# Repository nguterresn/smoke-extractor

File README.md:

# Welcome to the Smoke Extractor Repository!

Are you tired of inhaling smoke and fumes while soldering? Look no further! This portable smoke extractor is here to evolve your soldering experience.

This repository contains all the information you need to build your own smoke extractor using readily available components.

| [PCB](https://github.com/nguterresn/smoke-extractor/tree/master/pcb/1v1) | [STL](https://github.com/nguterresn/smoke-extractor/tree/master/stl) | [GERBER](https://github.com/nguterresn/smoke-extractor/blob/master/pcb/1v1/jlcpcb/production_files/GERBER-smoke_extractorV1_1.zip) | [BOM](https://github.com/nguterresn/smoke-extractor/blob/master/pcb/1v1/jlcpcb/production_files/BOM-smoke_extractorV1_1.csv) |
|-----|-----|--------|-----|

Below is a list of what you need. Let's start with the PCB:

* Take the [Bill of Materials](https://github.com/nguterresn/smoke-extractor/blob/master/pcb/1v1/jlcpcb/production_files/BOM-smoke_extractorV1_1.csv) and order from [LCSC](https://www.lcsc.com).
* Take the [compressed gerber files](https://github.com/nguterresn/smoke-extractor/blob/master/pcb/1v1/jlcpcb/production_files/GERBER-smoke_extractorV1_1.zip) and order the PCB from [JLCPCB](https://jlcpcb.com)

To 3D print the [enclosure](https://github.com/nguterresn/smoke-extractor/tree/master/stl/1v1), I would recommend to print it vertically with supports only where the PCB fits and at the top.

* You can find the files for the enclosure at [Thinginverse](https://www.thingiverse.com/thing:6496883) or on the [repository](https://github.com/nguterresn/smoke-extractor/tree/master/stl/1v1).
* You can find the sliced model and ready to print file for BambuLab printers here.

And finally, necessary items you can find in Amazon:

* Buy the Fume's filter. I took a [filter used on cat litter boxes](https://www.amazon.se/gp/product/B07WJ1Y1CH/ref=ppx_yo_dt_b_asin_title_o08_s00?ie=UTF8&psc=1) and trimmed it to 80x80mm.
* Buy a [80x80x25mm 12V fan](https://www.amazon.se/-/en/1-06W-80x80x25mm-56-1m³-2600U-EE80251S31000U999/dp/B07ZBNZQ2S/ref=sr_1_3?crid=MVLR8KCZBU2A&dib=eyJ2IjoiMSJ9.yyIoiUBXEqPdx7PXhLvxQ6DgrM7XN99XWWnRf-wjLIC2jV-B3UQ4XywT_NGIYMAKHvOpfRhJtW1-Edui-ORV4xDNA9OV7_BThwgb9X33OIwgTvXAGk9CamoQANMFjjYQfQlXwd1fQ9uBfTSz37shrT1HXBxxIDawscOyjEqbqhflptzGCS32OoU-07Krv_tXsq_2aFJ8kRP7iFG2Fm3--l_kvcWPGcEGKE2OmgzGbOBmr5wPGlOs1hTMt8ZC6lYbEhc1kAilJPhcBsXh4ESUahyO5wKTHMeF1VTbrVZGBB4.kkiZ6oj-aX831UgWn2JdLQOQZ6zxw4aFCHIgBYpVpvM&dib_tag=se&keywords=fan+80x80+12v&qid=1708787756&sprefix=fan+80x80+12v%2Caps%2C92&sr=8-3). Any fan should suffice (as long as is within 80x80x25mm), however some fans are specially built for increased air flow and low noise, such as [Noctua ones](https://www.amazon.se/-/en/Noctua-NF-R8-Redux-1800-PWM-performance/dp/B00KF7MVI2/ref=sr_1_3?crid=1FC5ZC8PZ4Y1V&dib=eyJ2IjoiMSJ9.nR2-oZtf9V-GN4B_sLLcsZsVkm8SOGSnasAzNeWOD6hcB3mSpQLWiwCVTJMJFPlbKCy_ke6oPzXiC_dCjItMRWk4W2Ovn52BVgXElBXkFmTP6l7XVI3kmm0ca1A7RbpRjykKHF7tixTPcCfjPfQAZWGbW_Z9oki_9TZgYak1CsVwYHUm23W-Hg3x731fiD-MuwIXEwUoA63P653yK8mSEY_l5Cigo0ODth0iAE_t3bkkZqnOJmHH7ZiWD8j_RxoCN1rxiMu7Us7g22hvU4B-fkI_2iGjdmFk5K9EcHZOC7k.gXca1K5ZeESalsrob-K74d8LU7yIyzcaKxv8FWTVuFg&dib_tag=se&keywords=noctua+80mm&qid=1708787907&sprefix=noctua+80m%2Caps%2C99&sr=8-3).
* Buy a [18350 battery holder from Amazon](https://www.amazon.se/-/en/3-7V-18650-Battery-Plastic-Storage/dp/B07MM1NHHL/ref=sr_1_3?crid=2S11BRPI1SFDN&dib=eyJ2IjoiMSJ9._ZvHPBCAkFADy9zm7AwcSj7BRWLtre4sQFriTdwADeFz38LD4PHVUqlo92Mr_qlHYvC9n_Wa976J5boEqPog5omuMcZvPQ4p1LHz4h0jg6txf33FL-gPQxLrHZZhL4yq8NlFmkt63MQLfnwRS_1h4xymLn59qeygErN50ODLHJ0hU8t5k7_wpVhyZUxli8YBID3BzOhYgPiTP1B--dGFmmnfPB8NTCn6rncl5h0IL3-LFAp2EmgDpC0F7w4vtddbEfQfdrLjZNarntx32AIs1I1Aa09CHDQLrP6kLzb9kvw.BXkkd7rySFMaa2OdXrMOJ7WG7TBaLJAFz9LXq7sVjNo&dib_tag=se&keywords=18350+battery+holder&qid=1708787362&sprefix=18350+battery+holder%2Caps%2C109&sr=8-3).

Once you have received everything you ordered, I recommend to use an hot air gun or a soldering plate to solder the PCB.

After the soldering process, I recommended soldering the fan power cables into the 12V and GND pads on the PCB, such that the fan is left connected to the PCB.

Start by adding the fan into the top part and match with the bottom pins.
Place the PCB; use two M3-5mm screws to fix it if the PCB is loose.

The cables are hidden below the fan and behind the PCB.

To assemble the back lid you will also need 2x M3-5mm screws and 2x M3-10mm screws.

Happy soldering!

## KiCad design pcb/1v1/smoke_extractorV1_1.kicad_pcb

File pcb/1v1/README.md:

On *CustomSymbols* - Project based symbols.

On *CustomFootprints* - Project based `.kicad_mod` footprints.

On *CustomSteps* - Project based `.step` files.

---

To add symbols to the project, open the file *CustomSymbols* (extension `.kicad_sym`) with a text editor and add the desired symbol as:

```md
(symbol "RA11131100" (in_bom yes) (on_board yes)
    (property "Reference" "U" (id 0) (at 0 0 0)
      (effects (font (size 1.27 1.27)))
    )
    (property "Value" "RA11131100" (id 1) (at 0 0 0)
      (effects (font (size 1.27 1.27)))
    )
    (property "Footprint" "" (id 2) (at 0 0 0)
      (effects (font (size 1.27 1.27)) hide)
    )
    (property "Datasheet" "" (id 3) (at 0 0 0)
      (effects (font (size 1.27 1.27)) hide)
    )
    (symbol "RA11131100_0_1"
      (rectangle (start -3.81 7.62) (end 3.81 2.54)
        (stroke (width 0.1524) (type default) (color 0 0 0 0))
        (fill (type none))
      )
      (arc (start -1.27 6.35) (mid -0.7022 5.0464) (end 0 3.81)
        (stroke (width 0.1524) (type default) (color 0 0 0 0))
        (fill (type none))
      )
    )
    (symbol "RA11131100_1_1"
      (pin power_in line (at -6.35 5.08 0) (length 2.54)
        (name "IN" (effects (font (size 1.27 1.27))))
        (number "1" (effects (font (size 1.27 1.27))))
      )
      (pin power_out line (at 6.35 5.08 180) (length 2.54)
        (name "OUT" (effects (font (size 1.27 1.27))))
        (number "2" (effects (font (size 1.27 1.27))))
      )
    )
)
``` 

The file `sym-lib-table` routes the project to the *CustomSymbols* folder.

---

To add footprints to the project, open the folder *CustomFootprints* and paste the desired `.kicad_mod` file.

The file `fp-lib-table` routes the project to the *CustomFootprints* folder.

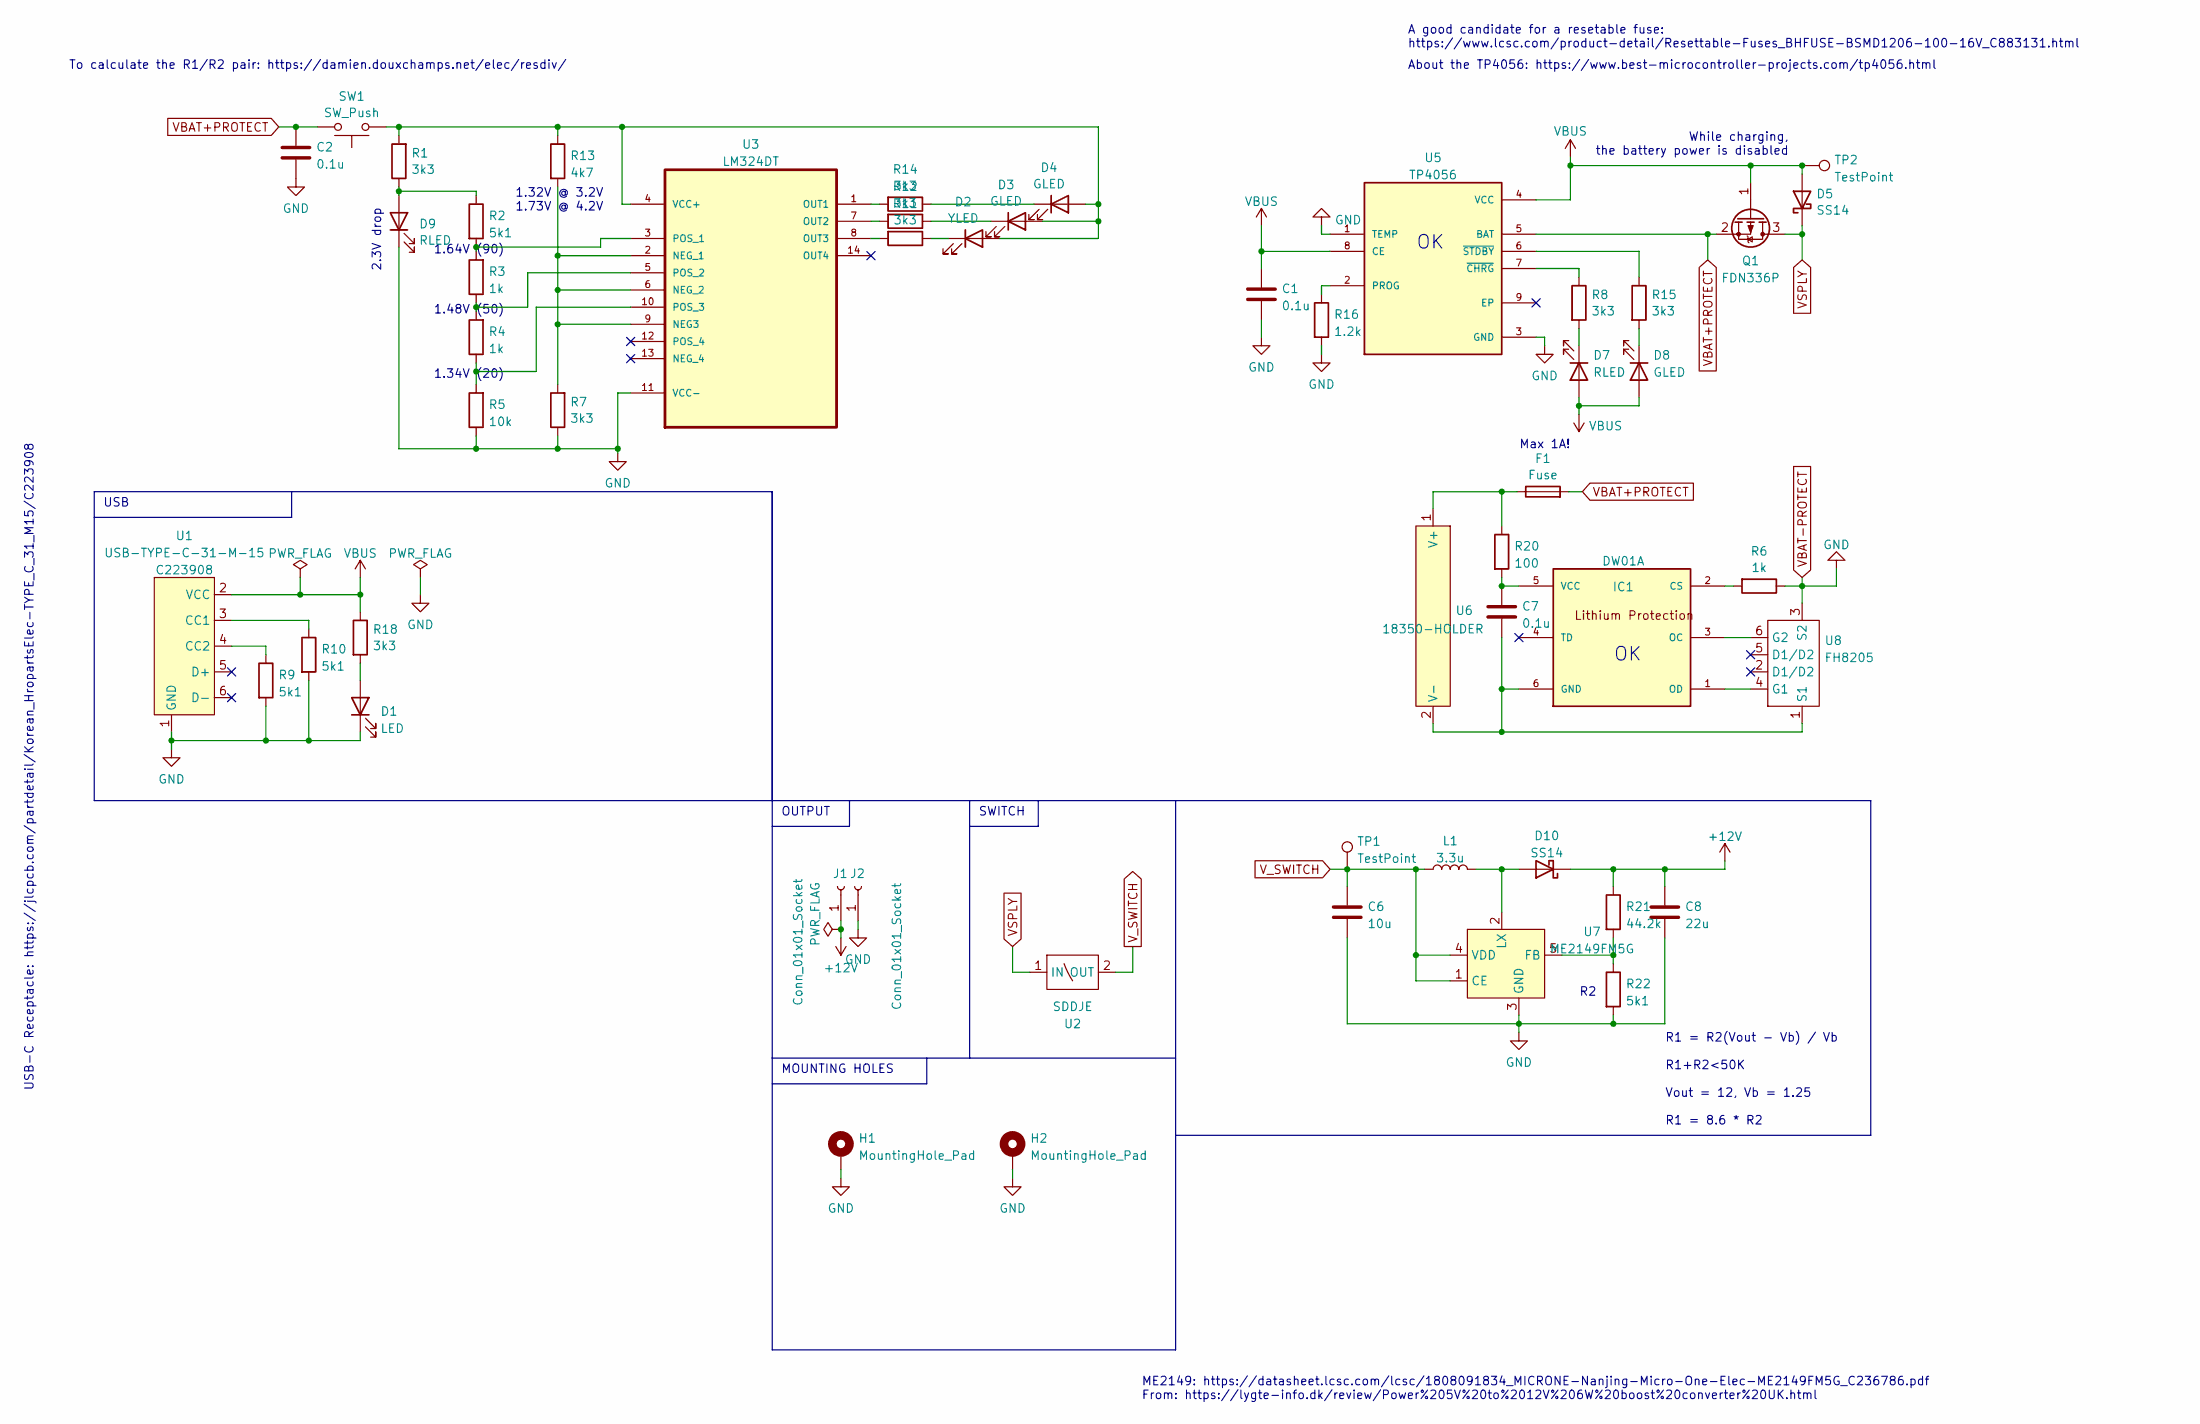
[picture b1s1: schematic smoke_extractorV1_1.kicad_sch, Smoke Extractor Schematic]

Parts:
C1, C2, C7: 0.1u; C_0603_1608Metric_Pad1.08x0.95mm_HandSolder; LCSC C30926
C6: 10u; C_0603_1608Metric_Pad1.08x0.95mm_HandSolder; LCSC C19702
C8: 22u; C_0805_2012Metric_Pad1.18x1.45mm_HandSolder; LCSC C98190
D1: LED; LED_0603_1608Metric_Pad1.05x0.95mm_HandSolder
D2: YLED; LED_0603_1608Metric_Pad1.05x0.95mm_HandSolder
D3, D4, D8: GLED; LED_0603_1608Metric_Pad1.05x0.95mm_HandSolder
D5, D10: SS14; D_SMA; LCSC C2480
D7, D9: RLED; LED_0603_1608Metric_Pad1.05x0.95mm_HandSolder
F1: Fuse; Fuse_0603_1608Metric_Pad1.05x0.95mm_HandSolder; LCSC C182303
H1, H2: MountingHole_Pad; MountingHole_3.2mm_M3_ISO7380_Pad
IC1: DW01A; SOT-23-6_Handsoldering; MPN DW01A; LCSC C351410
J1, J2: Conn_01x01_Socket; TestPoint_Pad_2.5x2.5mm
L1: 3.3u; L_Wuerth_WE-PD2-Typ-MS; LCSC C2929417
Q1: FDN336P; SOT-23; LCSC C475693
R1, R7, R8, R11, R12, R14, R15, R18: 3k3; R_0603_1608Metric_Pad0.98x0.95mm_HandSolder; LCSC C3017726
R2, R9, R10, R22: 5k1; R_0603_1608Metric_Pad0.98x0.95mm_HandSolder; LCSC C178023
R3, R4, R6: 1k; R_0603_1608Metric_Pad0.98x0.95mm_HandSolder; LCSC C328340
R5: 10k; R_0603_1608Metric_Pad0.98x0.95mm_HandSolder; LCSC C2930027
R13: 4k7; R_0603_1608Metric_Pad0.98x0.95mm_HandSolder; LCSC C105428
R16: 1.2k; R_0603_1608Metric_Pad0.98x0.95mm_HandSolder; LCSC C118396
R20: 100; R_0805_2012Metric_Pad1.20x1.40mm_HandSolder; LCSC C17408
R21: 44.2k; R_0603_1608Metric_Pad0.98x0.95mm_HandSolder; LCSC C23056
SW1: SW_Push; SW_PUSH_6mm
TP1, TP2: TestPoint; TestPoint_Pad_2.0x2.0mm
U1: USB-TYPE-C-31-M-15; LCSC C223908
U2: SDDJE; LCSC C358626
U3: LM324DT; SOIC127P600X175-14N; MPN LM324DT; LCSC C71035
U5: TP4056; SOP-8_3.9x4.9mm_P1.27mm; LCSC C16581
U6: 18350-HOLDER; 18350-Holder
U7: ME2149FM5G; SOT-23-5_HandSoldering; LCSC C236786
U8: FH8205; SOT-23-6_Handsoldering; LCSC C2928988

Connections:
+12V: C8.1, D10.1 (K), J1.1, R21.1
unnamed: D1.2 (A), R18.2
unnamed: D2.2 (A), D3.2 (A), D4.2 (A), R1.2, R13.1, SW1.1, U3.4 (VCC+)
unnamed: D2.1 (K), R11.1
unnamed: D3.1 (K), R12.1
unnamed: D4.1 (K), R14.1
unnamed: D7.1 (K), R8.2
unnamed: D8.1 (K), R15.2
unnamed: D9.2 (A), R1.1, R2.1
unnamed: D10.2 (A), L1.2, U7.2 (LX)
unnamed: IC1.2 (CS), R6.2
unnamed 11: C7.2, IC1.6 (GND), U6.2 (V-), U8.1 (S1); also elsewhere on the board
unnamed: IC1.3 (OC), U8.6 (G2)
unnamed: IC1.1 (OD), U8.4 (G1)
unnamed: C7.1, IC1.5 (VCC), R20.2
unnamed: R10.1, U1.3 (CC1)
unnamed: R9.1, U1.4 (CC2)
unnamed: R7.2, R13.2, U3.2 (NEG_1), U3.6 (NEG_2), U3.9 (NEG3)
unnamed: R14.2, U3.1 (OUT1)
unnamed: R12.2, U3.7 (OUT2)
unnamed: R11.2, U3.8 (OUT3)
unnamed: R2.2, R3.2, U3.3 (POS_1)
unnamed: R3.1, R4.2, U3.5 (POS_2)
unnamed: R4.1, R5.2, U3.10 (POS_3)
unnamed: R16.1, U5.2 (PROG)
unnamed: R8.1, U5.7 (~CHRG)
unnamed: R15.1, U5.6 (~STDBY)
unnamed 27: F1.1, R20.1, U6.1 (V+); also elsewhere on the board
unnamed: R21.2, R22.1, U7.5 (FB)
VBAT+PROTECT: C2.1, F1.2, Q1.2 (S), SW1.2, U5.5 (BAT)
VBAT-PROTECT: C1.2, C2.2, C6.2, C8.2, D1.1 (K), D9.1 (K), H1.1, H2.1, J2.1, R5.1, R6.1, R7.1, R9.2, R10.2, R16.2, R22.2, U1.1 (GND), U3.11 (VCC-), U5.1 (TEMP), U5.3 (GND), U7.3 (GND), U8.3 (S2)
VBUS: C1.1, D5.2 (A), D7.2 (A), D8.2 (A), Q1.1 (G), R18.1, TP2.1, U1.2 (VCC), U5.4 (VCC), U5.8 (CE)
VSPLY: D5.1 (K), Q1.3 (D), U2.1 (IN)
V_SWITCH: C6.1, L1.1, TP1.1, U2.2 (OUT), U7.1 (CE), U7.4 (VDD)

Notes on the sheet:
OUTPUT
1.32V @ 3.2V 1.73V @ 4.2V
2.3V drop
Max 1A!
A good candidate for a resetable fuse: https://www.lcsc.com/product-detail/Resettable-Fuses_BHFUSE-BSMD1206-100-16V_C883131.html
USB
About the TP4056: https://www.best-microcontroller-projects.com/tp4056.html
To calculate the R1/R2 pair: https://damien.douxchamps.net/elec/resdiv/
1.64V (90)
USB-C Receptacle: https://jlcpcb.com/partdetail/Korean_HropartsElec-TYPE_C_31_M15/C223908
MOUNTING HOLES
SWITCH
1.34V (20)
While charging, the battery power is disabled
1.48V (50)
R1 = R2(Vout - Vb) / Vb R1+R2<50K Vout = 12, Vb = 1.25 R1 = 8.6 * R2
ME2149: https://datasheet.lcsc.com/lcsc/1808091834_MICRONE-Nanjing-Micro-One-Elec-ME2149FM5G_C236786.pdf From: https://lygte-info.dk/review/Power%205V%20to%2012V%206W%20boost%20converter%20UK.html

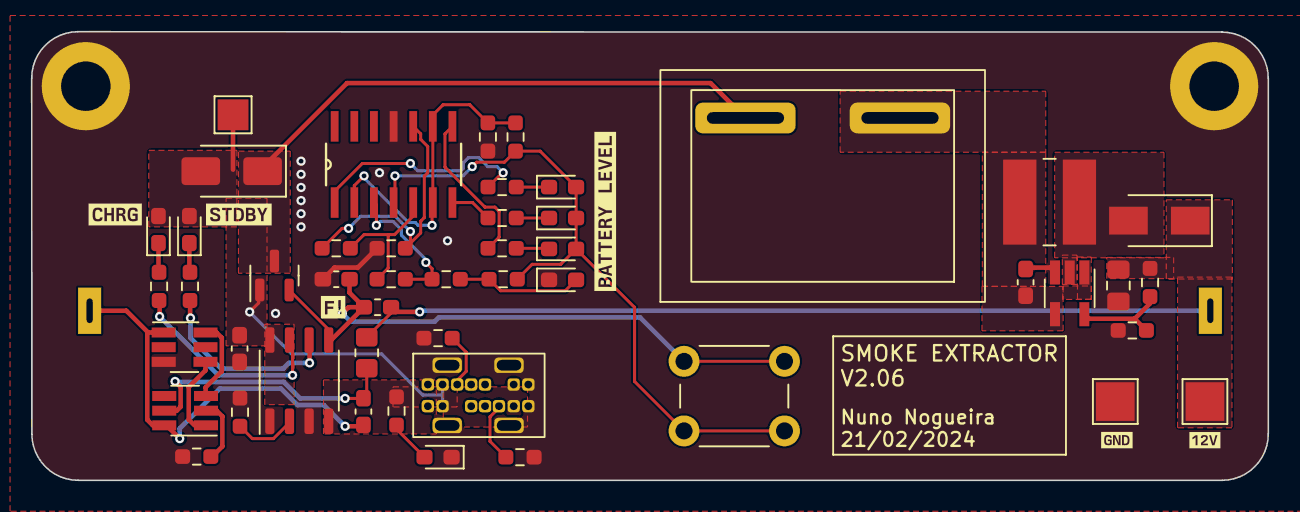
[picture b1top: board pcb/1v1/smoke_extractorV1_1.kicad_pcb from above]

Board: 2 copper layers, 80.0 x 29.0 mm, 57 parts (1 on the bottom side), 34 nets.

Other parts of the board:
kibuzzard-65B168C9: G***; kibuzzard-65B168C9
kibuzzard-65B169C7: G***; kibuzzard-65B169C7
kibuzzard-65B1691E: G***; kibuzzard-65B1691E
kibuzzard-65B1692F: G***; kibuzzard-65B1692F
kibuzzard-655136D6: G***; kibuzzard-655136D6
kibuzzard-655136E2: G***; kibuzzard-655136E2
locked: 18350-HOLDER; 18350-Holder

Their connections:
unnamed 11: locked.2 (V-); also elsewhere on the board
unnamed 27: locked.1 (V+); also elsewhere on the board

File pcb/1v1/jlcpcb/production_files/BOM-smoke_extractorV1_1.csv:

Comment,Designator,Footprint,LCSC
4k7,R13,R_0603_1608Metric_Pad0.98x0.95mm_HandSolder,C105428
1.2k,R16,R_0603_1608Metric_Pad0.98x0.95mm_HandSolder,C118396
TP4056,U5,SOP-8_3.9x4.9mm_P1.27mm,C16581
100,R20,R_0805_2012Metric_Pad1.20x1.40mm_HandSolder,C17408
5k1,"R10,R2,R22,R9",R_0603_1608Metric_Pad0.98x0.95mm_HandSolder,C178023
Fuse,F1,Fuse_0603_1608Metric_Pad1.05x0.95mm_HandSolder,C182303
10u,C6,C_0603_1608Metric_Pad1.08x0.95mm_HandSolder,C19702
USB-TYPE-C-31-M-15,U1,USB-TYPE-C-31-M-15,C223908
44.2k,R21,R_0603_1608Metric_Pad0.98x0.95mm_HandSolder,C23056
ME2149FM5G,U7,SOT-23-5_HandSoldering,C236786
SS14,"D10,D5",D_SMA,C2480
FH8205,U8,SOT-23-6_Handsoldering,C2928988
3.3u,L1,L_Wuerth_WE-PD2-Typ-MS,C2929417
10k,R5,R_0603_1608Metric_Pad0.98x0.95mm_HandSolder,C2930027
3k3,"R1,R11,R12,R14,R15,R18,R7,R8",R_0603_1608Metric_Pad0.98x0.95mm_HandSolder,C3017726
0.1u,"C1,C2,C7",C_0603_1608Metric_Pad1.08x0.95mm_HandSolder,C30926
1k,"R3,R4,R6",R_0603_1608Metric_Pad0.98x0.95mm_HandSolder,C328340
DW01A,IC1,SOT-23-6_Handsoldering,C351410
SDDJE,U2,SDDJE,C358626
FDN336P,Q1,SOT-23,C475693
LM324DT,U3,SOIC127P600X175-14N,C71035
22u,C8,C_0805_2012Metric_Pad1.18x1.45mm_HandSolder,C98190
TestPoint,TP2,TestPoint_Pad_2.0x2.0mm,
MountingHole_Pad,H2,MountingHole_3.2mm_M3_ISO7380_Pad,
YLED,D2,LED_0603_1608Metric_Pad1.05x0.95mm_HandSolder,
LED,D1,LED_0603_1608Metric_Pad1.05x0.95mm_HandSolder,
RLED,D7,LED_0603_1608Metric_Pad1.05x0.95mm_HandSolder,
GLED,D3,LED_0603_1608Metric_Pad1.05x0.95mm_HandSolder,
RLED,D9,LED_0603_1608Metric_Pad1.05x0.95mm_HandSolder,
MountingHole_Pad,H1,MountingHole_3.2mm_M3_ISO7380_Pad,
GLED,D8,LED_0603_1608Metric_Pad1.05x0.95mm_HandSolder,
SW_Push,SW1,SW_PUSH_6mm,
GLED,D4,LED_0603_1608Metric_Pad1.05x0.95mm_HandSolder,
Conn_01x01_Socket,J2,TestPoint_Pad_2.5x2.5mm,
Conn_01x01_Socket,J1,TestPoint_Pad_2.5x2.5mm,
18350-HOLDER,U6,18350-Holder,

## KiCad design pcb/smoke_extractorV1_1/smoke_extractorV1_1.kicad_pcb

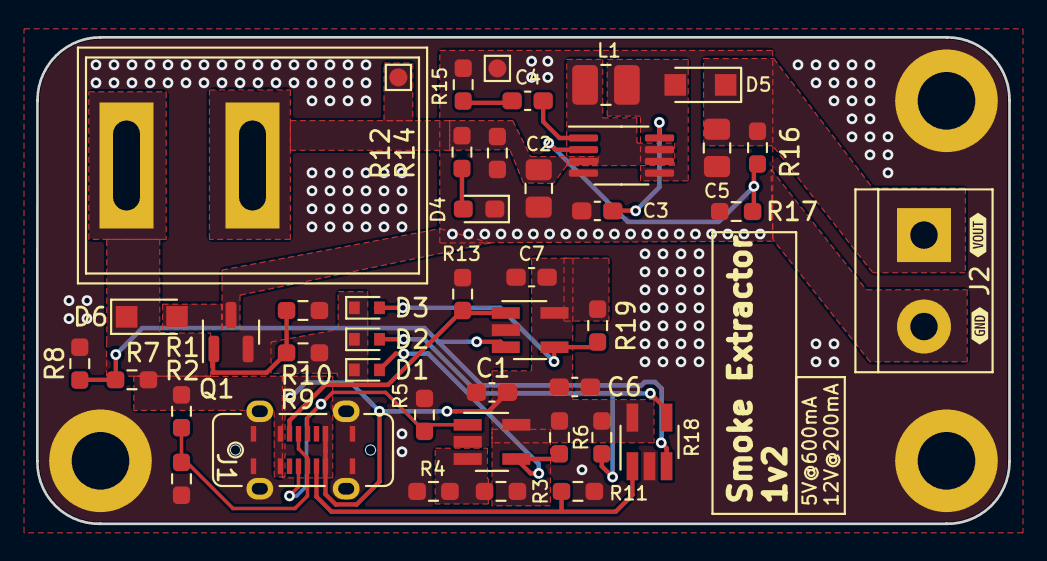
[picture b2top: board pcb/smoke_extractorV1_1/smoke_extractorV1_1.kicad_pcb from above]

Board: 2 copper layers, 54.0 x 27.0 mm, 46 parts (0 on the bottom side), 22 nets.

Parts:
C1, C6, C7: 0.1u; C_0603_1608Metric_Pad1.08x0.95mm_HandSolder
C2, C5: 10u; C_0805_2012Metric_Pad1.18x1.45mm_HandSolder
C3: 10n; C_0603_1608Metric_Pad1.08x0.95mm_HandSolder
C4: 2.2n; C_0603_1608Metric_Pad1.08x0.95mm_HandSolder
D1, D2, D3: D; D_SOD-523
D4: LED; LED_0603_1608Metric_Pad1.05x0.95mm_HandSolder
D5, D6: SS34; Nexperia_CFP3_SOD-123W
H1, H2, H3: MountingHole_Pad; MountingHole_3.2mm_M3_ISO7380_Pad
J1: USB_C_Receptacle; USB4120-03-C
J2: Screw_Terminal_01x02; TerminalBlock_bornier-2_P5.08mm
L1: 4.7u; L_1008_2520Metric_Pad1.43x2.20mm_HandSolder
Q1: AO3400A; SOT-23
R1, R3, R5, R7: 47k; R_0603_1608Metric_Pad0.98x0.95mm_HandSolder
R2: 6k8; R_0603_1608Metric_Pad0.98x0.95mm_HandSolder
R4: 4k7; R_0603_1608Metric_Pad0.98x0.95mm_HandSolder
R6, R10, R18, R19: 5k1; R_0603_1608Metric_Pad0.98x0.95mm_HandSolder
R8: 7k6; R_0603_1608Metric_Pad0.98x0.95mm_HandSolder
R9: 100; R_0603_1608Metric_Pad0.98x0.95mm_HandSolder
R11, R13: 5.1k; R_0603_1608Metric_Pad0.98x0.95mm_HandSolder
R12: 1k; R_0603_1608Metric_Pad0.98x0.95mm_HandSolder
R14: 100k; R_0603_1608Metric_Pad0.98x0.95mm_HandSolder
R15: 15k; R_0603_1608Metric_Pad0.98x0.95mm_HandSolder
R16: 86.6k; R_0603_1608Metric_Pad0.98x0.95mm_HandSolder
R17: 12k; R_0603_1608Metric_Pad0.98x0.95mm_HandSolder
U1, U4, U5: LMV331; SOT-23-5_HandSoldering
U2: RA11131100
U3: MP1542; MSOP-8_3x3mm_P0.65mm
kibuzzard-631C7DF6: G***; kibuzzard-631C7DF6
kibuzzard-631C7E0D: G***; kibuzzard-631C7E0D

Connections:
CC1: J1.A5 (CC1), R11.2, U4.1 (+)
CC1_DET: D2.2 (A), R18.1, U4.4
CC2: J1.B5 (CC2), R13.2, U5.1 (+)
CC2_DET: D3.2 (A), R19.1, U5.4
CHG_DET: D1.2 (A), R6.1, U1.4
D+: J1.A6 (D+), J1.B6 (D+), R1.1, R2.2
D-: J1.A7 (D-), J1.B7 (D-), R5.1, U1.1 (+)
GND: C1.2, C6.2, C7.2, H1.1, H2.1, H3.1, J1.A1 (GND), J1.A12 (GND), J1.B1 (GND), J1.B12 (GND), J1.S1 (SHIELD), Q1.2 (S), R2.1, R4.1, R5.2, R8.1, R10.2, R11.1, R13.1, U1.2 (V-), U4.2 (V-), U5.2 (V-)
unnamed: C3.1, U3.8 (SS)
unnamed: C4.1, U3.1 (COMP)
unnamed: C4.2, R15.1
unnamed: D1.1 (K), D2.1 (K), D3.1 (K), R9.2
unnamed: D4.2 (A), R12.2
unnamed: D5.2 (A), L1.2, U3.5 (SW)
unnamed: Q1.1 (G), R9.1, R10.1
unnamed: R16.2, R17.1, U3.2 (FB)
VBOOST_OUT: C5.1, D5.1 (K), J2.1, R16.1
VBUS_DRAIN: C2.2, C3.2, C5.2, D4.1 (K), D6.2 (A), J2.2, Q1.3 (D), R14.2, R15.2, R17.2, U3.4 (GND)
VBUS_OPEN: C1.1, C6.1, C7.1, D6.1 (K), J1.A4 (VBUS), J1.A9 (VBUS), J1.B4 (VBUS), J1.B9 (VBUS), R1.2, R3.2, R6.2, R7.2, R18.2, R19.2, U1.5 (V+), U2.1 (IN), U4.5 (V+), U5.5 (V+)
VBUS_SWITCH: C2.1, L1.1, R12.1, R14.1, U2.2 (OUT), U3.3 (EN), U3.6 (IN), U3.7 (FSEL)
VDAT_REF: R3.1, R4.2, U1.3 (-)
V_CC_REF: R7.1, R8.2, U4.3 (-), U5.3 (-)

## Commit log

2022-07-04 changed folders and started pcb design all over again
2022-07-09 Some important docs
2022-07-11 New smoke extractor version. WIP
2022-07-13 Added the first comparator for the USB Data lines
2022-07-13 updated gitignore to not include the backups
2022-07-13 Added comparators circuit (D lines and CC lines) to the schematic
2022-07-13 Added missing comparator for the CC2 line.
2022-07-13 Added a comment
2022-07-16 Added boost symbol + circuit
2022-07-16 Final schematics tweaks and BOM
2022-07-17 Ready to start designing!
2022-07-17 Added overvoltage IC
2022-07-20 Some more improvements. First idea of design (traces and zones still missing)
    Also need to:
    - Change the USB C to a horizontal footprint
    - Use an extended switch with screw terminal
2022-07-26 More improvements in the pcb design
2022-07-28 Removed the voltage IC and one mounting hole. Missing boost converter conns only.
2022-07-30 Ready to place the order.
2022-07-30 Error checks.
2022-07-30 Exported gerber
2022-08-02 Schematic as pdf
2022-08-03 Reorganized repo
2022-08-03 Removed old images.
2022-08-13 Added BOM
2022-09-10 Version 1.2
2022-09-10 Added testing pads for version 1.2
2022-09-10 Removed out of date files
2022-09-29 Updated gerber files.
2022-10-09 Added stl files.
2022-10-16 Created latest bom
2023-01-26 Updated stls.
2023-01-29 added with-battery designs
2023-01-31 Changed folder name.
2023-02-01 ignore .gcode files.
2023-02-03 added pinout diagram
2023-02-03 not on this repo.
2023-03-12 smoke extractor 2.0
2023-05-06 cleaned a bit
2023-05-06 version 2.01 ready to order
2023-10-01 v2.02
2023-11-30 version 2,03 and 2.04!
2024-01-04 new version 2.04
2024-01-24 Version 2.05
2024-02-20 v2.06
2024-02-21 Removed some files and so one
2024-02-21 more changes.
2024-02-26 last stl
2024-03-02 support for Noctua NF-R8 redux-1800
